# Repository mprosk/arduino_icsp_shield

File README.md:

# Arduino ICSP Shield
UNO shield for using an Arduino as an in-circuit programmer

Onboard logic level shifter. Selectable target voltage (5V or 3V3)

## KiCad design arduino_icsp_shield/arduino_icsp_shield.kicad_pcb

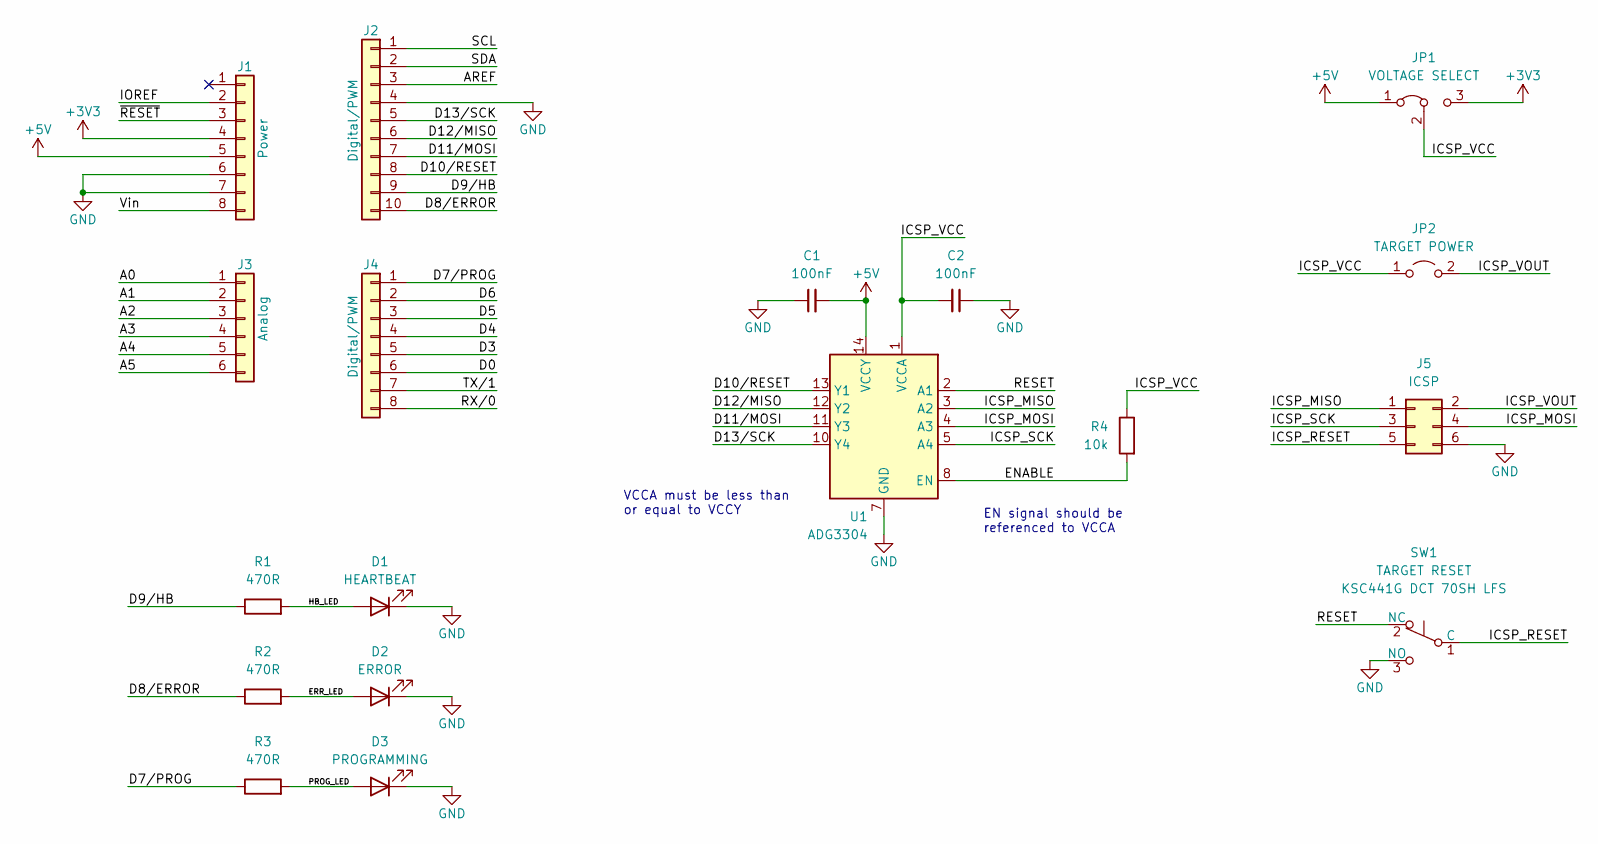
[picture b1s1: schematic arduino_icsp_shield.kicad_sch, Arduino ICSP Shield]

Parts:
C1, C2: 100nF; C_0603_1608Metric
D1: HEARTBEAT; LED_D3.0mm
D2: ERROR; LED_D3.0mm
D3: PROGRAMMING; LED_D3.0mm
J1: Power; PinHeader_1x08_P2.54mm_Vertical
J2: Digital/PWM; PinHeader_1x10_P2.54mm_Vertical
J3: Analog; PinHeader_1x06_P2.54mm_Vertical
J4: Digital/PWM; PinHeader_1x08_P2.54mm_Vertical
J5: ICSP; IDC-Header_2x03_P2.54mm_Vertical
JP1: VOLTAGE SELECT; PinHeader_1x03_P2.54mm_Vertical
JP2: TARGET POWER; PinHeader_1x02_P2.54mm_Vertical
R1, R2, R3: 470R; R_0805_2012Metric
R4: 10k; R_0805_2012Metric
SW1: TARGET RESET; SW_Push_SPDT_CK_KSC4xxG; Part KSC441G DCT 70SH LFS
U1: ADG3304; TSSOP-14_4.4x5mm_P0.65mm

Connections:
+3V3: J1.4, JP1.3 (B)
+5V: C1.2, J1.5, JP1.1 (A), U1.14 (VCCY)
/A0: J3.1
/A1: J3.2
/A2: J3.3
/A3: J3.4
/A4: J3.5
/A5: J3.6
/AREF: J2.3
/D0: J4.6
/D3: J4.5
/D4: J4.4
/D5: J4.3
/D6: J4.2
/D7/PROG: J4.1, R3.1
/D8/ERROR: J2.10, R2.1
/D9/HB: J2.9, R1.1
/D10/RESET: J2.8, U1.13 (Y1)
/D11/MOSI: J2.7, U1.11 (Y3)
/D12/MISO: J2.6, U1.12 (Y2)
/D13/SCK: J2.5, U1.10 (Y4)
/ENABLE: R4.2, U1.8 (EN)
/ERR_LED: D2.2 (A), R2.2
/HB_LED: D1.2 (A), R1.2
/ICSP_MISO: J5.1, U1.3 (A2)
/ICSP_MOSI: J5.4, U1.4 (A3)
/ICSP_RESET: J5.5, SW1.1 (C)
/ICSP_SCK: J5.3, U1.5 (A4)
/ICSP_VCC: C2.2, JP1.2 (C), JP2.1 (A), R4.1, U1.1 (VCCA)
/ICSP_VOUT: J5.2, JP2.2 (B)
/IOREF: J1.2
/PROG_LED: D3.2 (A), R3.2
/RESET: SW1.2 (NC), U1.2 (A1)
/RX/0: J4.8
/SCL: J2.1
/SDA: J2.2
/TX/1: J4.7
/Vin: J1.8
/~RESET: J1.3
GND: C1.1, C2.1, D1.1 (K), D2.1 (K), D3.1 (K), J1.6, J1.7, J2.4, J5.6, SW1.3 (NO), U1.7 (GND)

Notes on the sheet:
VCCA must be less than or equal to VCCY
EN signal should be referenced to VCCA

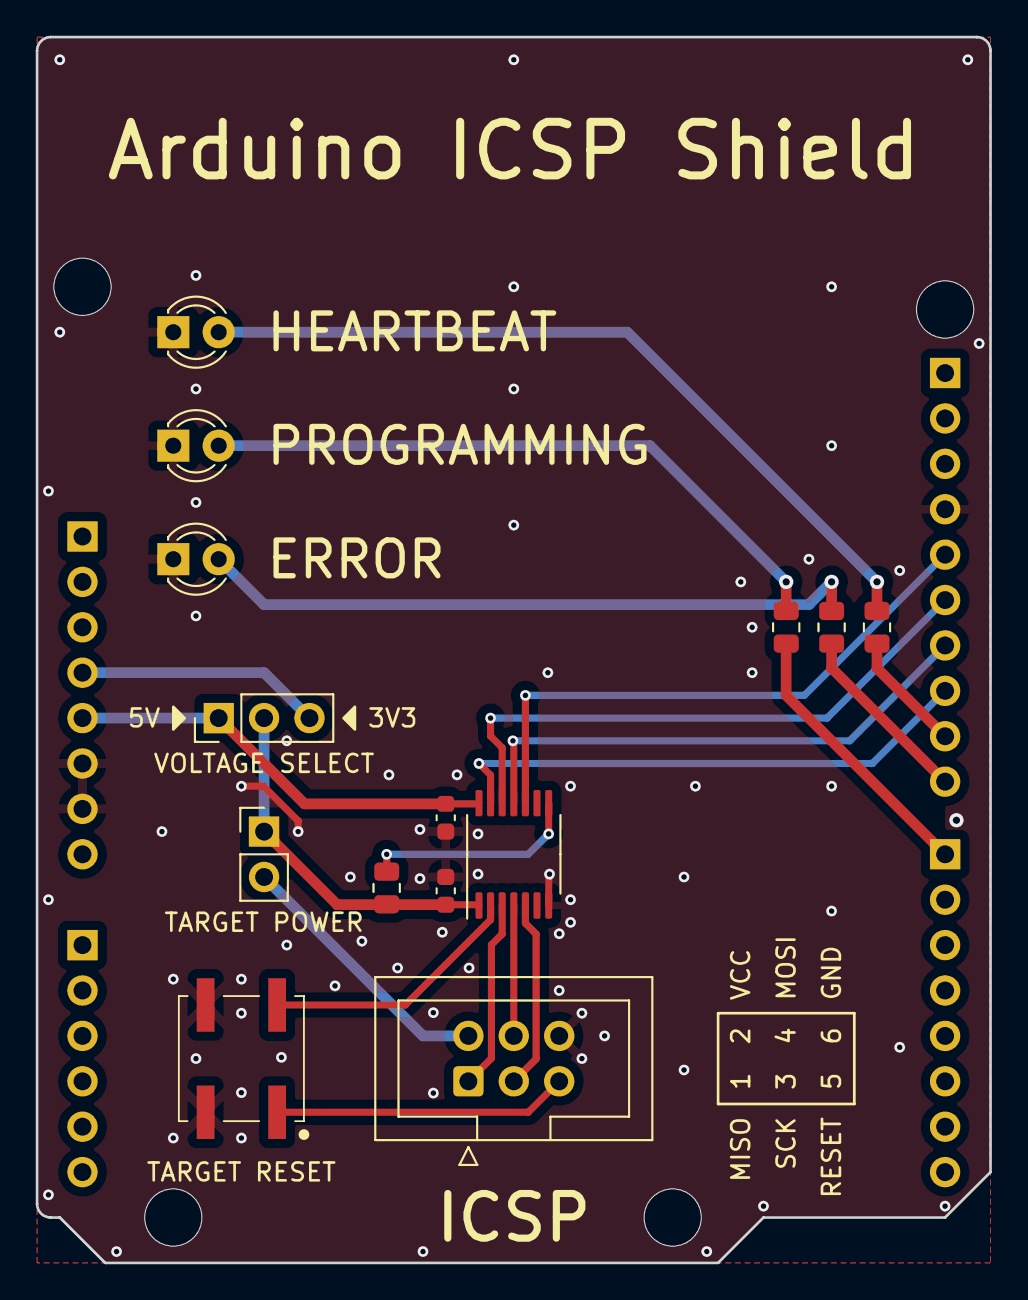
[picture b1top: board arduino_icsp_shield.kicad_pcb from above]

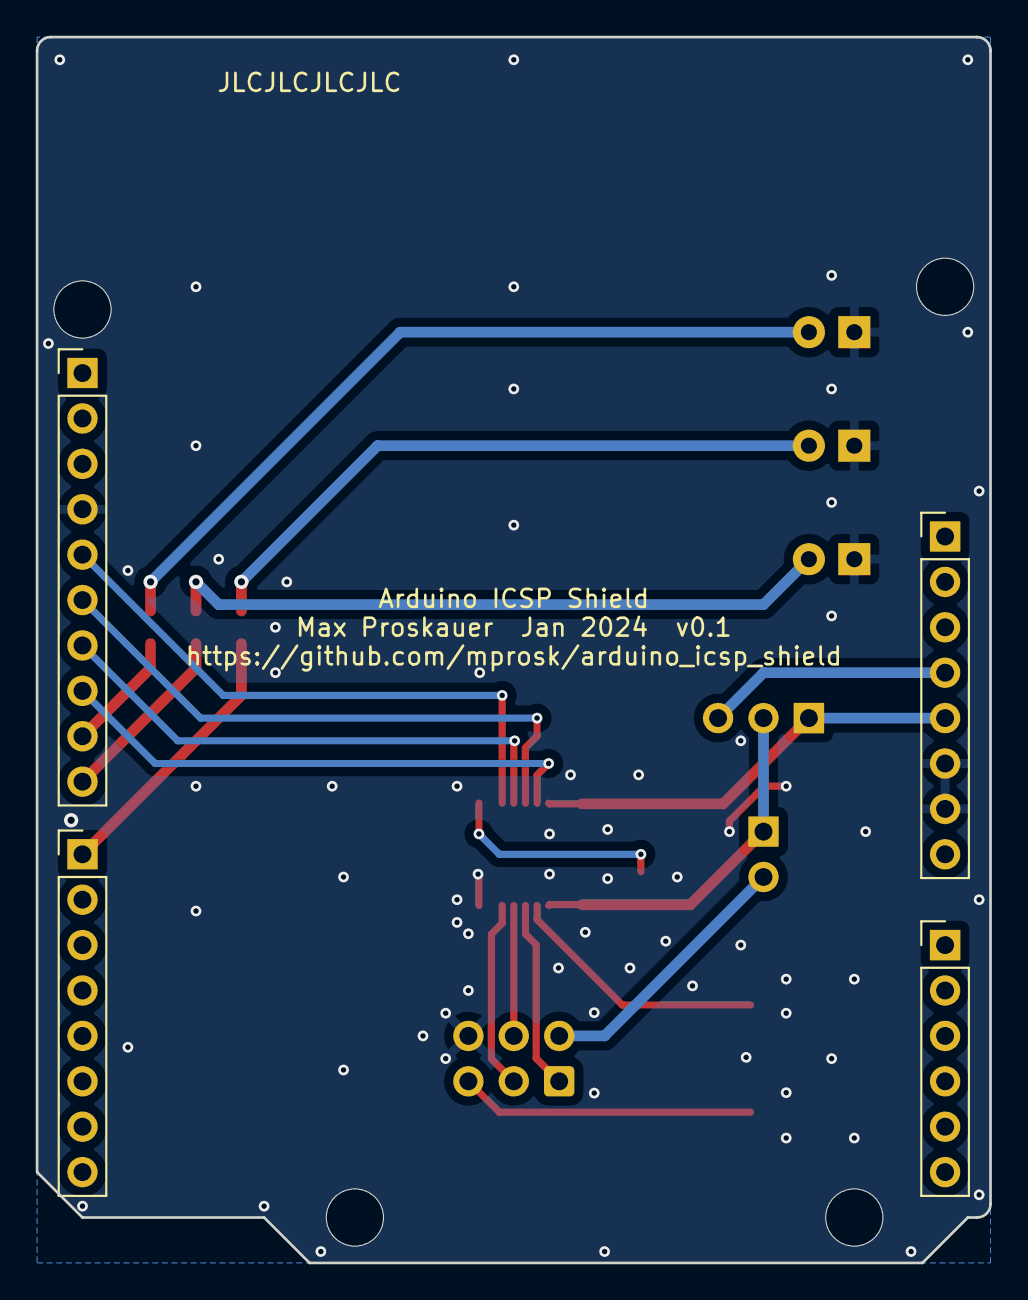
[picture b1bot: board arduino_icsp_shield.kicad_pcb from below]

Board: 2 copper layers, 53.3 x 68.6 mm, 22 parts (4 on the bottom side), 21 nets.

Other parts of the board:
MH1, MH2, MH3, MH4: MountingHole_3.2mm

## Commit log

2024-01-23 Complete schematic and layout
2024-01-23 Export gerbers
2024-01-23 Update readme add PDF schematic
2024-01-23 Rename gerber zip
2024-01-23 Update gitignore
2024-01-23 Fix which voltage the level shifter enable is coming from
2024-01-23 Tweak resistor placement
